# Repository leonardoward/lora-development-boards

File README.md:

# RFM95W-915S2 Development Board #

This repository contains the design of a development board for the RFM95W-915S2. The PCB was designed using KiCad.

The [RFM95W-915S2 Development board](https://hackaday.io/project/173457/log/196116-lora-rfm95w-915s2-development-board) is a PCB that contains a RFM95W LoRa transceiver, a [U.FL connector](https://www.digikey.com/en/products/detail/hirose-electric-co-ltd/U-FL-R-SMT-1-10/2391570) for the external antenna, a decoupling capacitor and a group of headers connected to the different pins of the transceiver. The transceiver can be used as a sender or a receiver.

## Table of Contents

1. [Schematic](#schematic)
2. [Bill of Materials](#bill-of-materials)
3. [3D Model](#3d-model)
4. [Firmware and Testing](#firmware-and-testing)
5. [Authors](#authors)

## Schematic ##

**[Back to top](#table-of-contents)**

## Bill of Materials ##

| Reference | Quantity |
| ------------- | ------------- |
| [RFM95W-915S2 LoRa™ Transceiver Module 915MHz SMD](https://www.digikey.com/en/products/detail/rf-solutions/RFM95W-915S2/6564923)  | 1 |
| [10 µF ±10% 6.3V Ceramic Capacitor 0805](https://www.digikey.com/en/products/detail/samsung-electro-mechanics/CL21A106KQCLNNC/3888062)  | 1 |
| [U.FL (UMCC) Connector Receptacle, Male Pin 50 Ohm SMD](https://www.digikey.com/en/products/detail/hirose-electric-co-ltd/U-FL-R-SMT-1-10/2391570) | 1 |
| [Conn Header 40POS 2.54](https://www.digikey.com/en/products/detail/3m/2340-6111TG/1237275) | 1 |

**[Back to top](#table-of-contents)**

## 3D Model ##

**[Back to top](#table-of-contents)**

## Firmware and Testing ##

The webpage randomnerdtutorials.com has an amazing tutorial named [ESP32 with LoRa using Arduino IDE – Getting Started](https://randomnerdtutorials.com/esp32-lora-rfm95-transceiver-arduino-ide/), that tutorial contains detailed information about how to use the RFM95 with an ESP32 (the same microcontroller that was selected for our designs). I used the same firmware and connections provided by the tutorial.

The test requires 2 transceivers, one of them will be used as a sender and the other as a receiver. In this case, one of the transceivers is the  RFM95W-915S2 Development board and the other one is the [RFM95W transceiver from Adafruit](https://www.digikey.com/en/products/detail/adafruit-industries-llc/3072/6005357).

The connections are the following:

| ESP32 | RFM95W-915S2 Development Board |
| ------------- | ------------- |
| 3V3  | 3.3V |
| GND  | GND |
| GPIO 14  | RST |
| GPIO 5  | CS |
| GPIO 18  | SCK |
| GPIO 23  | MOSI |
| GPIO 19  | 	MISO |

| ESP32 | RFM95W Board from Adafruit |
| ------------- | ------------- |
| 3V3  | VIN |
| GND  | GND |
| GPIO 14  | RST |
| GPIO 5  | CS |
| GPIO 18  | SCK |
| GPIO 23  | MOSI |
| GPIO 19  | 	MISO |

This repository contains a folder named /Firmware/ that contains the project for the transceiver as a [receiver](https://github.com/leonardoward/lora-development-boards/blob/main/Firmware/esp32_RFM95_receiver/esp32_RFM95_receiver.ino) and a [sender](https://github.com/leonardoward/lora-development-boards/blob/main/Firmware/esp32_RFM95_sender/esp32_RFM95_sender.ino).  

Both of the RFM95W Boards were used as a sender and receiver, the result was successful in both cases. During the test, one of the transceivers sends the package "hello counter", where the counter is a number that goes from 0 to 32767. The other transceiver receives the package and prints the message through serial.

### Requisites ###

1. [ESP32 Add-on in Arduino IDE](https://randomnerdtutorials.com/installing-the-esp32-board-in-arduino-ide-windows-instructions/)
2. [LoRa Library](https://randomnerdtutorials.com/esp32-lora-rfm95-transceiver-arduino-ide/)

Results visualized in the serial monitor from the receiver circuit:

For more information about the firmware visit the [original tutorial for the RFM95W](https://randomnerdtutorials.com/esp32-lora-rfm95-transceiver-arduino-ide/).

**[Back to top](#table-of-contents)**

## Authors ##

* **[Leonardo Ward](https://github.com/leonardoward)**

**[Back to top](#table-of-contents)**

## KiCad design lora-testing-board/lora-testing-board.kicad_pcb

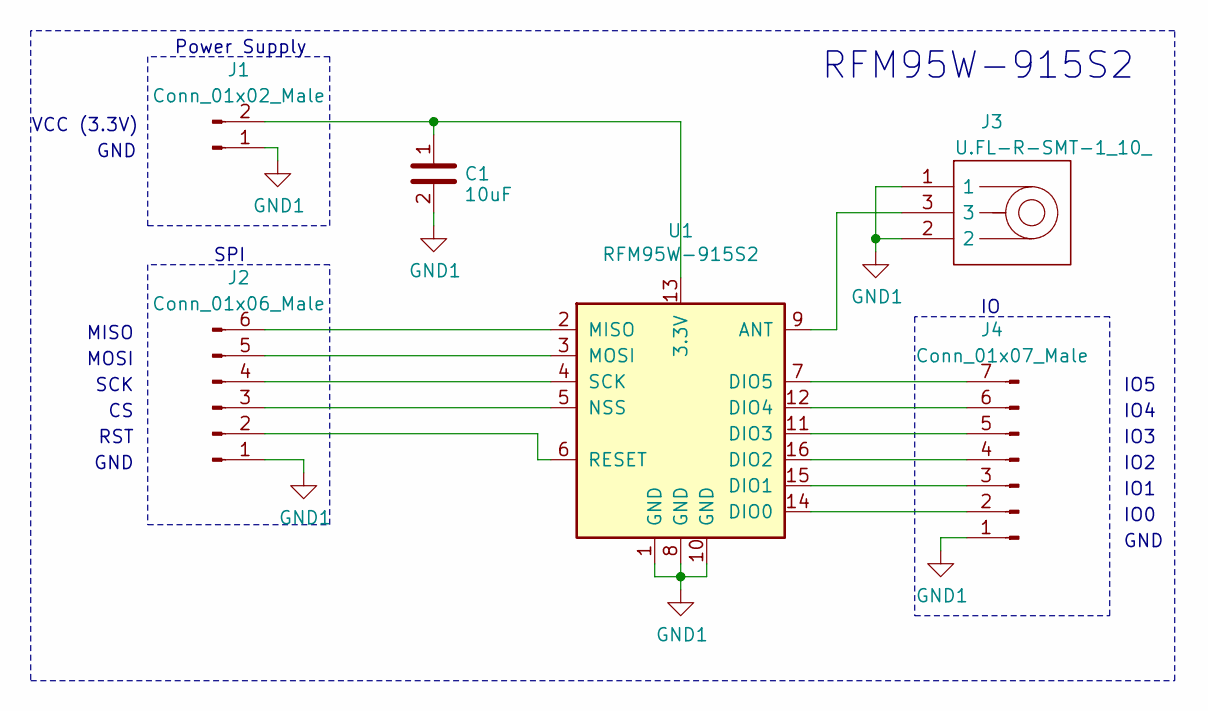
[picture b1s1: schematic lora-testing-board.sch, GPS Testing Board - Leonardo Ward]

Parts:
C1: 10uF; C_0805_2012Metric; Manufacturer Part Number CL21A106KQCLNNC
J1: Conn_01x02_Male; PinSocket_1x02_P2.54mm_Vertical
J2: Conn_01x06_Male; PinSocket_1x06_P2.54mm_Vertical
J3: U.FL-R-SMT-1_10_; Manufacturer Part Number U.FL-R-SMT-1(10)
J4: Conn_01x07_Male; PinSocket_1x07_P2.54mm_Vertical
U1: RFM95W-915S2; HOPERF_RFM9XW_SMD

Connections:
GND1: C1.2, J1.1, J2.1, J3.1, J3.2, J4.1, U1.1 (GND), U1.8 (GND), U1.10 (GND)
unnamed: C1.1, J1.2, U1.13 (3.3V)
unnamed: J2.2, U1.6 (RESET)
unnamed: J2.3, U1.5 (NSS)
unnamed: J2.4, U1.4 (SCK)
unnamed: J2.5, U1.3 (MOSI)
unnamed: J2.6, U1.2 (MISO)
unnamed: J3.3, U1.9 (ANT)
unnamed: J4.2, U1.14 (DIO0)
unnamed: J4.3, U1.15 (DIO1)
unnamed: J4.4, U1.16 (DIO2)
unnamed: J4.5, U1.11 (DIO3)
unnamed: J4.6, U1.12 (DIO4)
unnamed: J4.7, U1.7 (DIO5)

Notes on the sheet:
Power Supply
SPI
VCC (3.3V)
GND
SCK
MOSI
MISO
RST
IO5
IO4
IO3
IO2
IO1
IO0
RFM95W-915S2

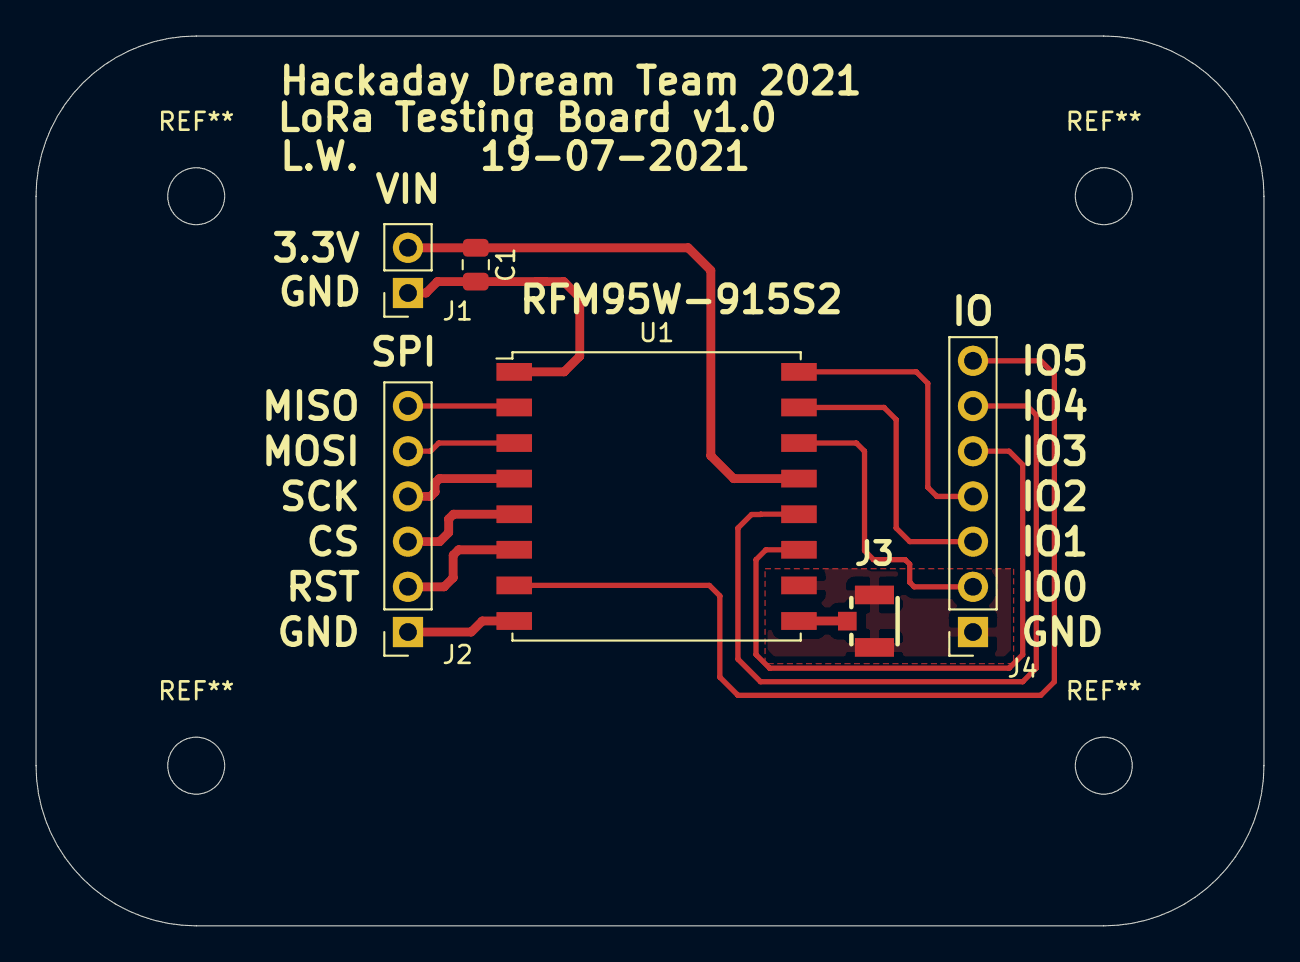
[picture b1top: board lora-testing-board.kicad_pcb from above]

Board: 2 copper layers, 69.0 x 50.0 mm, 6 parts (0 on the bottom side), 14 nets.

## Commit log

2021-07-14 Added libraries
2021-07-18 Added schematic for RFM95W
2021-07-18 Added PCB for RFM95W-915S2
2021-07-20 Added IDFv3 and Gerber
2021-08-02 Updated schematic, gerbers and added README
2021-08-02 Added info in README
2021-08-19 Added firmware
2021-09-21 Added images
